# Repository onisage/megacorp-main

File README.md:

# MEGACORP-main
For all MEGACORP-related projects.

Created in collaboration with [baconspoon](github.com/baconspoon85) and [apfel](https://github.com/kilipan).

## Row Stagger

## Ortholinear

## Alpha Stagger

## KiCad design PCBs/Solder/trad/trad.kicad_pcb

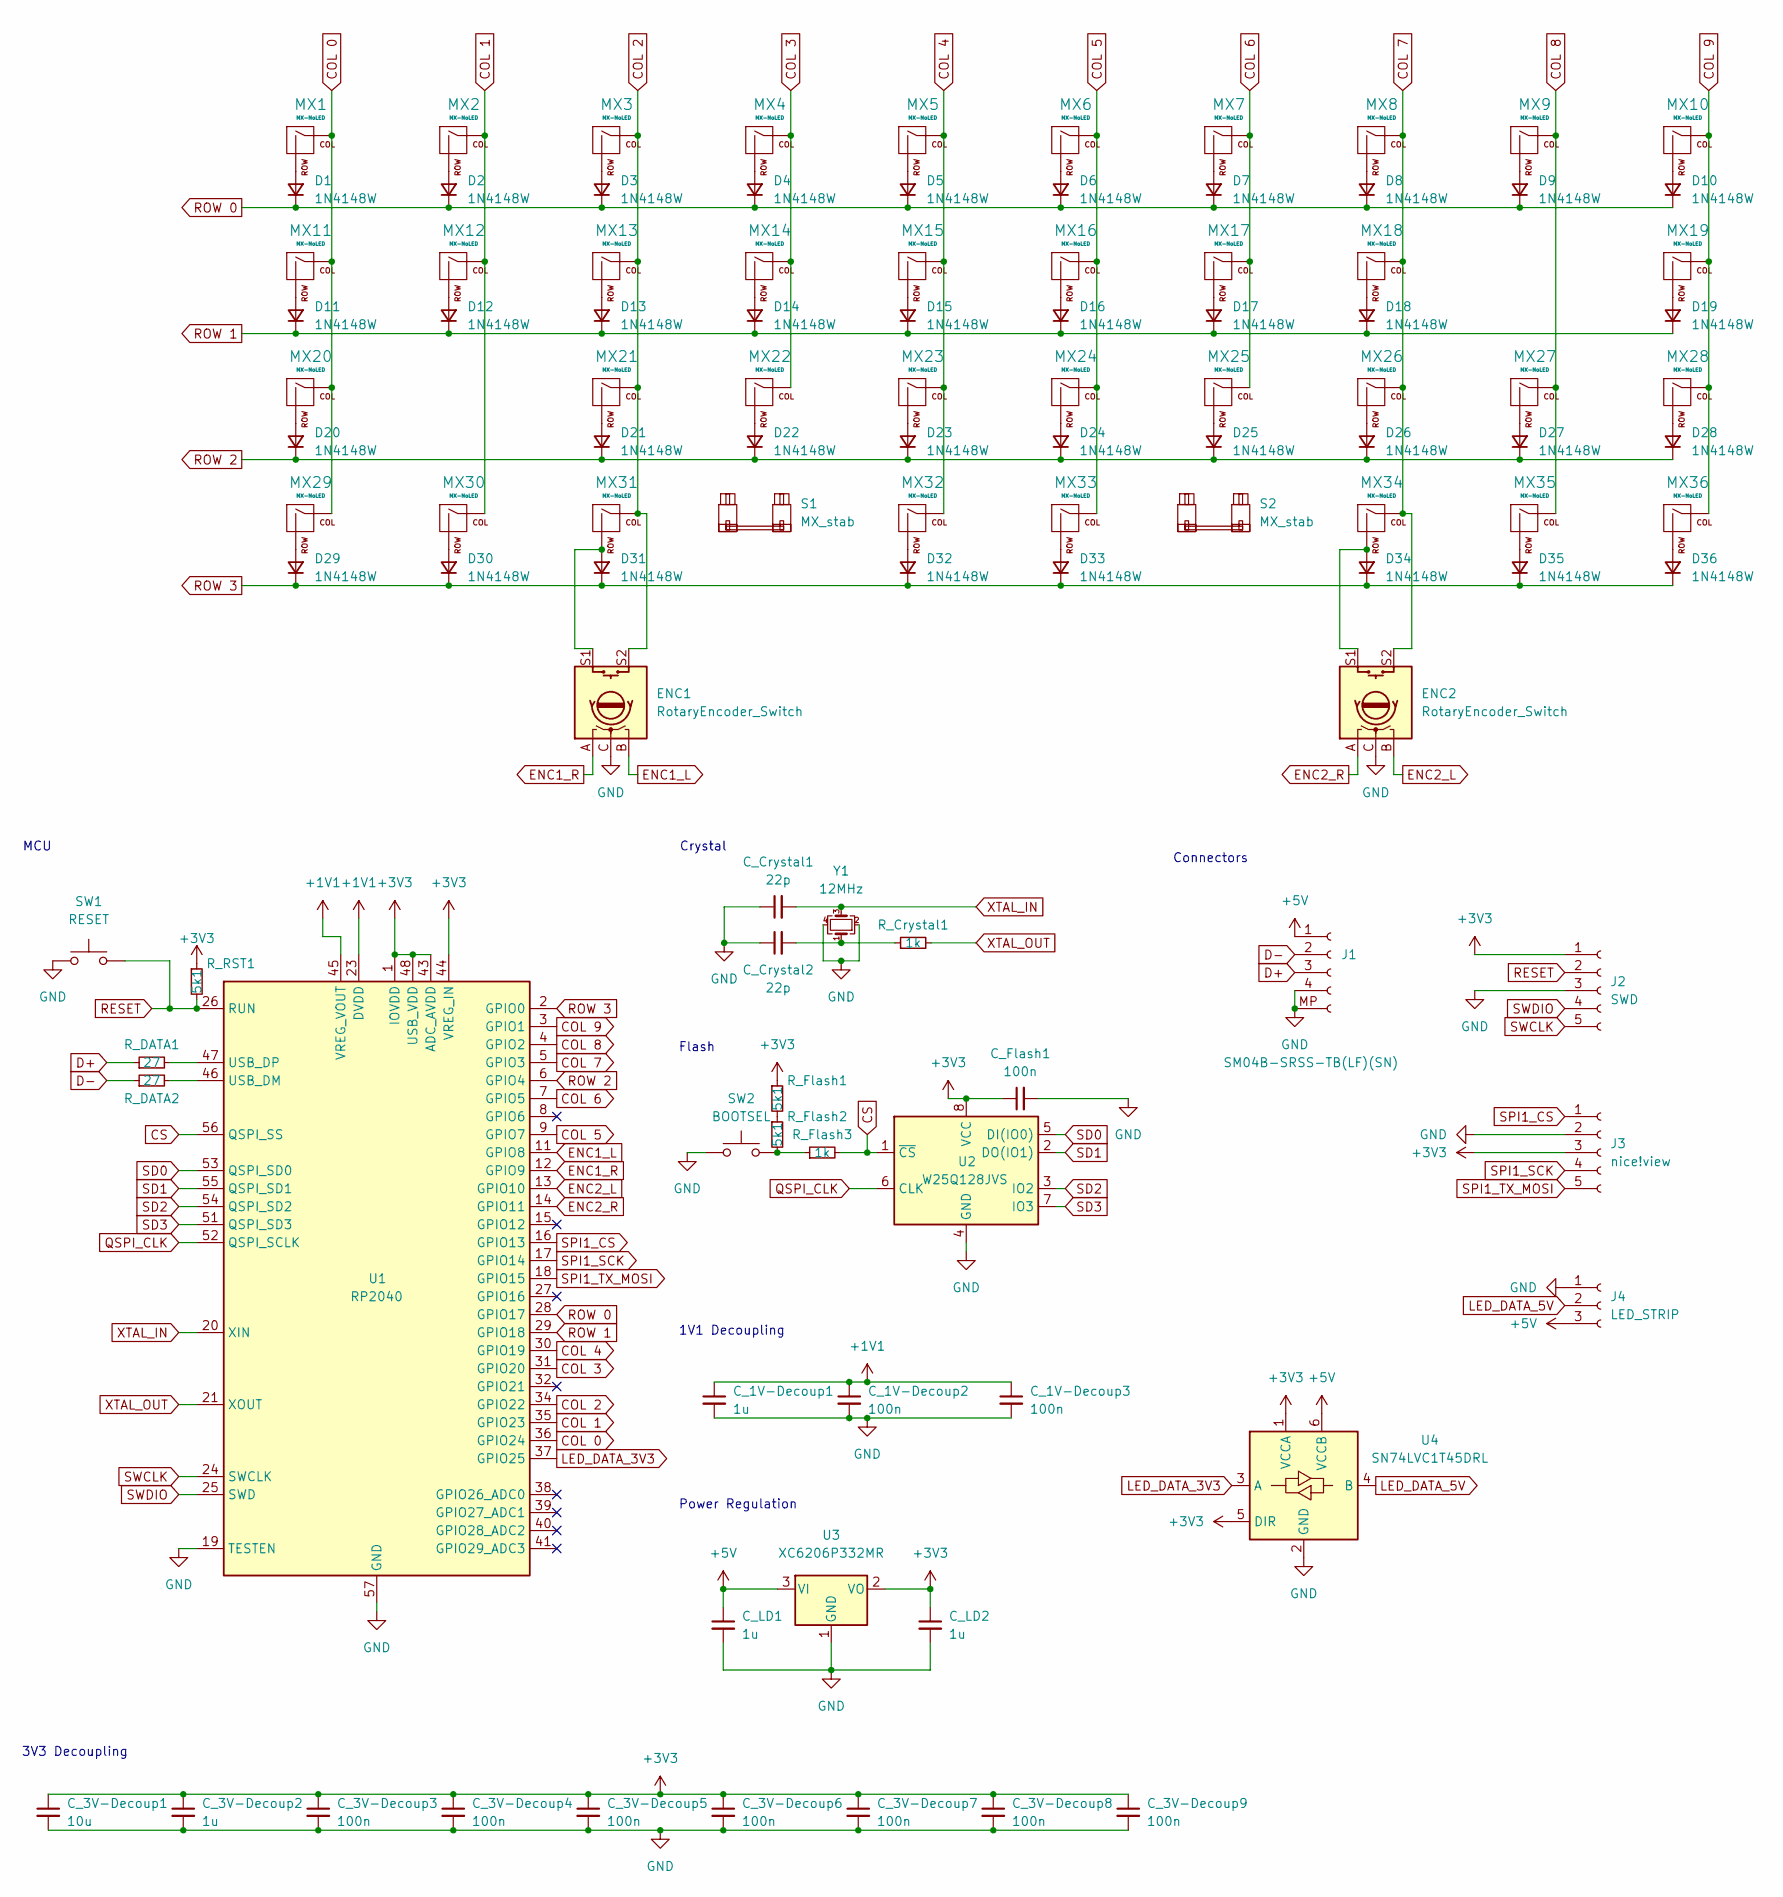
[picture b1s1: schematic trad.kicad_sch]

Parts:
C_1V-Decoup1, C_3V-Decoup2: 1u; C_0402_1005Metric
C_1V-Decoup2, C_1V-Decoup3, C_3V-Decoup3, C_3V-Decoup4, C_3V-Decoup5, C_3V-Decoup6, C_3V-Decoup7, C_3V-Decoup8, C_3V-Decoup9: 100n; C_0402_1005Metric
C_3V-Decoup1: 10u; C_0402_1005Metric
C_Crystal1, C_Crystal2: 22p; C_0402_1005Metric
C_Flash1: 100n; C_0402_1005Metric
C_LD1, C_LD2: 1u; C_0402_1005Metric
D1, D2, D3, D4, D5, D6, D7, D8, D9, D10, D11, D12, D13, D14, D15, D16, D17, D18, D19, D20, D21, D22, D23, D24, D25, D26, D27, D28, D29, D30, D31, D32, D33, D34, D35, D36: 1N4148W; D_SOD-123
ENC1, ENC2: RotaryEncoder_Switch; ROT_Alps_EC11E-Switch
J1: SM04B-SRSS-TB(LF)(SN); JST_SH_SM04B-SRSS-TB_1x04-1MP_P1.00mm_Horizontal; LCSC C160404
J2: SWD; PinHeader_1x05_P2.54mm_Vertical
J3: nice!view; PinHeader_1x05_P2.54mm_Vertical
J4: LED_STRIP; PinHeader_1x03_P2.54mm_Vertical
MX1, MX2, MX3, MX4, MX5, MX6, MX7, MX8, MX9, MX10, MX12, MX13, MX14, MX15, MX16, MX17, MX18, MX21, MX22, MX23, MX24, MX25, MX26, MX27, MX29, MX30, MX31, MX34, MX35, MX36: MX-NoLED; SW_Hybrid_Cherry_MX_Alps_1.00u
MX11, MX28: MX-NoLED; SW_Hybrid_Cherry_MX_Alps_1.25u
MX19, MX20: MX-NoLED; SW_Hybrid_Cherry_MX_Alps_1.75u
MX32, MX33: MX-NoLED; SW_Hybrid_Cherry_MX_Alps_2.00u
R_Crystal1: 1k; R_0402_1005Metric
R_DATA1, R_DATA2: 27; R_0402_1005Metric
R_Flash1, R_Flash2: 5k1; R_0402_1005Metric
R_Flash3: 1k; R_0402_1005Metric
R_RST1: 5k1; R_0402_1005Metric
S1, S2: MX_stab; STAB_MX_2u
SW1: RESET; SW_SPST_TL3342; LCSC C318884
SW2: BOOTSEL; SW_SPST_TL3342; LCSC C318884
U1: RP2040; QFN-56-1EP_7x7mm_P0.4mm_EP3.2x3.2mm_ThermalVias; LCSC C2040
U2: W25Q128JVS; SOIC-8_5.23x5.23mm_P1.27mm; LCSC C2613930
U3: XC6206P332MR; SOT-23; LCSC C5446
U4: SN74LVC1T45DRL; SOT-563
Y1: 12MHz; Crystal_SMD_3225-4Pin_3.2x2.5mm; LCSC C9002

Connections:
+1V1: C_1V-Decoup1.1, C_1V-Decoup2.1, C_1V-Decoup3.1, U1.23 (DVDD), U1.45 (VREG_VOUT), U1.50 (DVDD)
+3V3: C_3V-Decoup1.1, C_3V-Decoup2.1, C_3V-Decoup3.1, C_3V-Decoup4.1, C_3V-Decoup5.1, C_3V-Decoup6.1, C_3V-Decoup7.1, C_3V-Decoup8.1, C_3V-Decoup9.1, C_Flash1.1, C_LD2.1, J2.1, J3.3, R_Flash1.1, R_RST1.1, U1.1 (IOVDD), U1.10 (IOVDD), U1.22 (IOVDD), U1.33 (IOVDD), U1.42 (IOVDD), U1.43 (ADC_AVDD), U1.44 (VREG_IN), U1.48 (USB_VDD), U1.49 (IOVDD), U2.8 (VCC), U3.2 (VO), U4.1 (VCCA), U4.5 (DIR)
+5V: C_LD1.1, J1.1, J4.3, U3.3 (VI), U4.6 (VCCB)
COL 0: MX1.1 (COL), MX11.1 (COL), MX20.1 (COL), MX29.1 (COL), U1.36 (GPIO24)
COL 1: MX2.1 (COL), MX12.1 (COL), MX30.1 (COL), U1.35 (GPIO23)
COL 2: ENC1.S2, MX3.1 (COL), MX13.1 (COL), MX21.1 (COL), MX31.1 (COL), U1.34 (GPIO22)
COL 3: MX4.1 (COL), MX14.1 (COL), MX22.1 (COL), U1.31 (GPIO20)
COL 4: MX5.1 (COL), MX15.1 (COL), MX23.1 (COL), MX32.1 (COL), U1.30 (GPIO19)
COL 5: MX6.1 (COL), MX16.1 (COL), MX24.1 (COL), MX33.1 (COL), U1.9 (GPIO7)
COL 6: MX7.1 (COL), MX17.1 (COL), MX25.1 (COL), U1.7 (GPIO5)
COL 7: ENC2.S2, MX8.1 (COL), MX18.1 (COL), MX26.1 (COL), MX34.1 (COL), U1.5 (GPIO3)
COL 8: MX9.1 (COL), MX27.1 (COL), MX35.1 (COL), U1.4 (GPIO2)
COL 9: MX10.1 (COL), MX19.1 (COL), MX28.1 (COL), MX36.1 (COL), U1.3 (GPIO1)
CS: R_Flash3.2, U1.56 (QSPI_SS), U2.1 (~CS)
D+: J1.3, R_DATA1.1
D-: J1.2, R_DATA2.1
ENC1_L: ENC1.B, U1.11 (GPIO8)
ENC1_R: ENC1.A, U1.12 (GPIO9)
ENC2_L: ENC2.B, U1.13 (GPIO10)
ENC2_R: ENC2.A, U1.14 (GPIO11)
GND: C_1V-Decoup1.2, C_1V-Decoup2.2, C_1V-Decoup3.2, C_3V-Decoup1.2, C_3V-Decoup2.2, C_3V-Decoup3.2, C_3V-Decoup4.2, C_3V-Decoup5.2, C_3V-Decoup6.2, C_3V-Decoup7.2, C_3V-Decoup8.2, C_3V-Decoup9.2, C_Crystal1.1, C_Crystal2.1, C_Flash1.2, C_LD1.2, C_LD2.2, ENC1.C, ENC2.C, J1.4, J1.MP, J2.3, J3.2, J4.1, SW1.1, SW2.1, U1.19 (TESTEN), U1.57 (GND), U2.4 (GND), U3.1 (GND), U4.2 (GND), Y1.2, Y1.4
LED_DATA_3V3: U1.37 (GPIO25), U4.3 (A)
LED_DATA_5V: J4.2, U4.4 (B)
unnamed: C_Crystal2.2, R_Crystal1.1, Y1.1
unnamed: D1.2 (A), MX1.2 (ROW)
unnamed: D2.2 (A), MX2.2 (ROW)
unnamed: D3.2 (A), MX3.2 (ROW)
unnamed: D4.2 (A), MX4.2 (ROW)
unnamed: D5.2 (A), MX5.2 (ROW)
unnamed: D6.2 (A), MX6.2 (ROW)
unnamed: D7.2 (A), MX7.2 (ROW)
unnamed: D8.2 (A), MX8.2 (ROW)
unnamed: D9.2 (A), MX9.2 (ROW)
unnamed: D10.2 (A), MX10.2 (ROW)
unnamed: D11.2 (A), MX11.2 (ROW)
unnamed: D12.2 (A), MX12.2 (ROW)
unnamed: D13.2 (A), MX13.2 (ROW)
unnamed: D14.2 (A), MX14.2 (ROW)
unnamed: D15.2 (A), MX15.2 (ROW)
unnamed: D16.2 (A), MX16.2 (ROW)
unnamed: D17.2 (A), MX17.2 (ROW)
unnamed: D18.2 (A), MX18.2 (ROW)
unnamed: D19.2 (A), MX19.2 (ROW)
unnamed: D20.2 (A), MX20.2 (ROW)
unnamed: D21.2 (A), MX21.2 (ROW)
unnamed: D22.2 (A), MX22.2 (ROW)
unnamed: D23.2 (A), MX23.2 (ROW)
unnamed: D24.2 (A), MX24.2 (ROW)
unnamed: D25.2 (A), MX25.2 (ROW)
unnamed: D26.2 (A), MX26.2 (ROW)
unnamed: D27.2 (A), MX27.2 (ROW)
unnamed: D28.2 (A), MX28.2 (ROW)
unnamed: D29.2 (A), MX29.2 (ROW)
unnamed: D30.2 (A), MX30.2 (ROW)
unnamed: D31.2 (A), ENC1.S1, MX31.2 (ROW)
unnamed: D32.2 (A), MX32.2 (ROW)
unnamed: D33.2 (A), MX33.2 (ROW)
unnamed: D34.2 (A), ENC2.S1, MX34.2 (ROW)
unnamed: D35.2 (A), MX35.2 (ROW)
unnamed: D36.2 (A), MX36.2 (ROW)
unnamed: R_Flash1.2, R_Flash2.1
unnamed: R_Flash2.2, R_Flash3.1, SW2.2
unnamed: R_DATA2.2, U1.46 (USB_DM)
unnamed: R_DATA1.2, U1.47 (USB_DP)
QSPI_CLK: U1.52 (QSPI_SCLK), U2.6 (CLK)
RESET: J2.2, R_RST1.2, SW1.2, U1.26 (RUN)
ROW 0: D1.1 (K), D2.1 (K), D3.1 (K), D4.1 (K), D5.1 (K), D6.1 (K), D7.1 (K), D8.1 (K), D9.1 (K), D10.1 (K), U1.28 (GPIO17)
ROW 1: D11.1 (K), D12.1 (K), D13.1 (K), D14.1 (K), D15.1 (K), D16.1 (K), D17.1 (K), D18.1 (K), D19.1 (K), U1.29 (GPIO18)
ROW 2: D20.1 (K), D21.1 (K), D22.1 (K), D23.1 (K), D24.1 (K), D25.1 (K), D26.1 (K), D27.1 (K), D28.1 (K), U1.6 (GPIO4)
ROW 3: D29.1 (K), D30.1 (K), D31.1 (K), D32.1 (K), D33.1 (K), D34.1 (K), D35.1 (K), D36.1 (K), U1.2 (GPIO0)
SD0: U1.53 (QSPI_SD0), U2.5 (DI(IO0))
SD1: U1.55 (QSPI_SD1), U2.2 (DO(IO1))
SD2: U1.54 (QSPI_SD2), U2.3 (IO2)
SD3: U1.51 (QSPI_SD3), U2.7 (IO3)
SPI1_CS: J3.1, U1.16 (GPIO13)
SPI1_SCK: J3.4, U1.17 (GPIO14)
SPI1_TX_MOSI: J3.5, U1.18 (GPIO15)
SWCLK: J2.5, U1.24 (SWCLK)
SWDIO: J2.4, U1.25 (SWD)
XTAL_IN: C_Crystal1.2, U1.20 (XIN), Y1.3
XTAL_OUT: R_Crystal1.2, U1.21 (XOUT)

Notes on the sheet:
Power Regulation
Flash
MCU
3V3 Decoupling
Connectors
1V1 Decoupling
Crystal

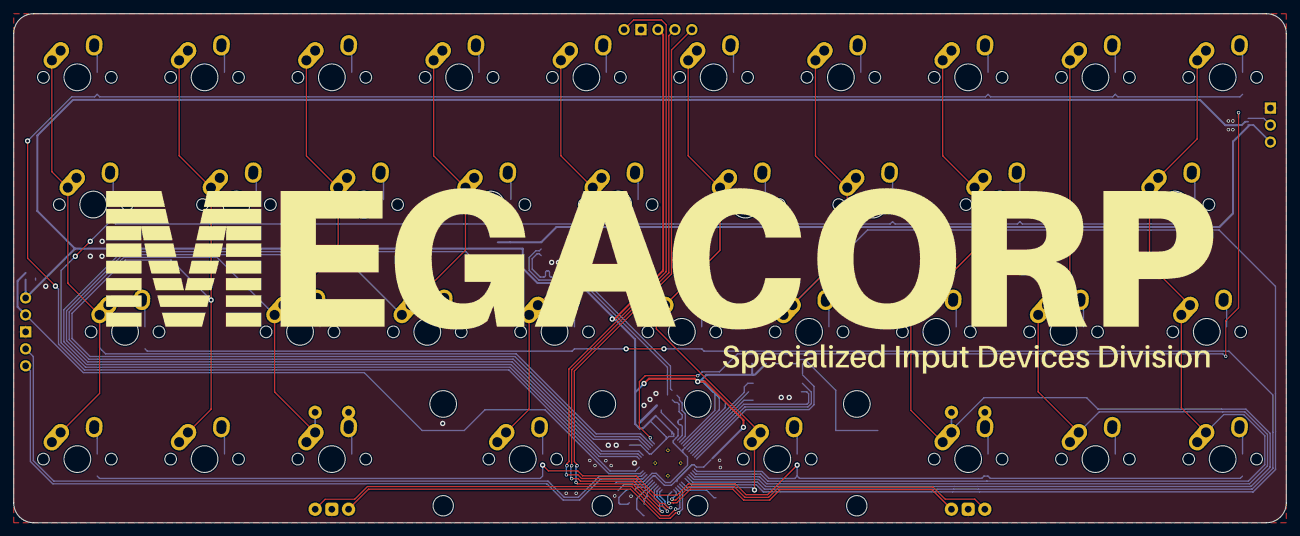
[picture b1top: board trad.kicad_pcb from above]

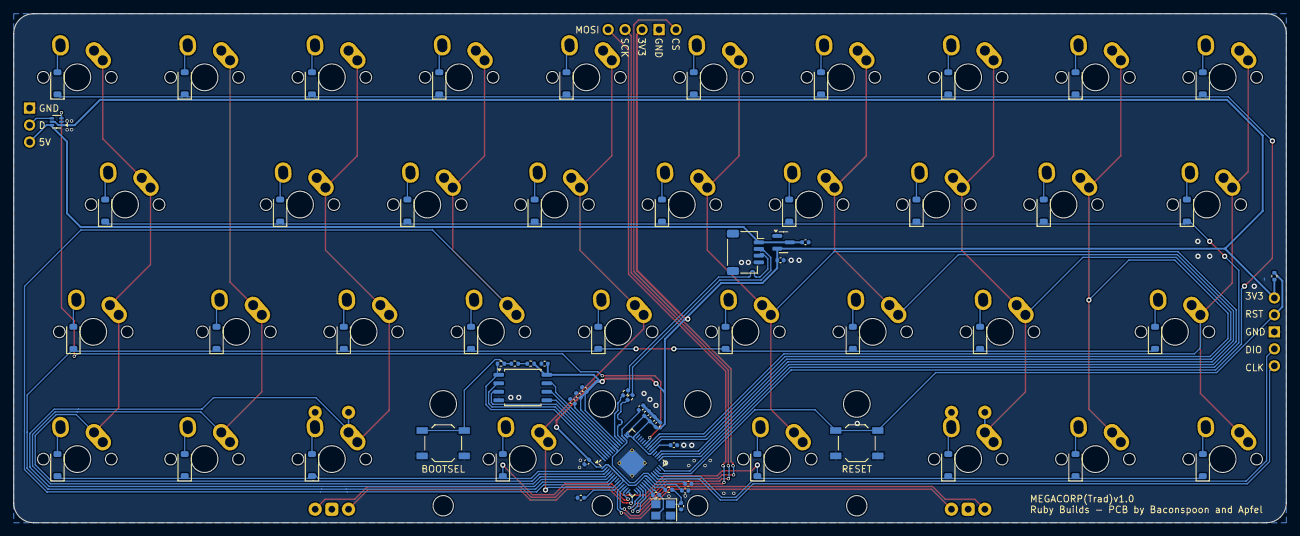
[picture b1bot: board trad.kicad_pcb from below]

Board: 2 copper layers, 190.5 x 76.2 mm, 111 parts (69 on the bottom side), 81 nets.

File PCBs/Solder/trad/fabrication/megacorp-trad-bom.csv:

Comment,Designator,Footprint,JLCPCB Part#(optional)
1uF,C_1V-Decoup1,C_0402_1005Metric,C52923
100nF,C_1V-Decoup2,C_0402_1005Metric,C2655418
100nF,C_1V-Decoup3,C_0402_1005Metric,C2655418
10uF,C_3V-Decoup1,C_0402_1005Metric,C19702
1uF,C_3V-Decoup2,C_0402_1005Metric,C52923
100nF,C_3V-Decoup3,C_0402_1005Metric,C2655418
100nF,C_3V-Decoup4,C_0402_1005Metric,C2655418
100nF,C_3V-Decoup5,C_0402_1005Metric,C2655418
100nF,C_3V-Decoup6,C_0402_1005Metric,C2655418
100nF,C_3V-Decoup7,C_0402_1005Metric,C2655418
100nF,C_3V-Decoup8,C_0402_1005Metric,C2655418
100nF,C_3V-Decoup9,C_0402_1005Metric,C2655418
22pF,C_Crystal1,C_0402_1005Metric,C1555
22pF,C_Crystal2,C_0402_1005Metric,C1555
100nF,C_Flash1,C_0402_1005Metric,C2655418
1uF,C_LD1,C_0402_1005Metric,C52923
1uF,C_LD2,C_0402_1005Metric,C52923
1N4148W,D1,D_SOD-123,C81598
1N4148W,D2,D_SOD-123,C81598
1N4148W,D3,D_SOD-123,C81598
1N4148W,D4,D_SOD-123,C81598
1N4148W,D5,D_SOD-123,C81598
1N4148W,D6,D_SOD-123,C81598
1N4148W,D7,D_SOD-123,C81598
1N4148W,D8,D_SOD-123,C81598
1N4148W,D9,D_SOD-123,C81598
1N4148W,D10,D_SOD-123,C81598
1N4148W,D11,D_SOD-123,C81598
1N4148W,D12,D_SOD-123,C81598
1N4148W,D13,D_SOD-123,C81598
1N4148W,D14,D_SOD-123,C81598
1N4148W,D15,D_SOD-123,C81598
1N4148W,D16,D_SOD-123,C81598
1N4148W,D17,D_SOD-123,C81598
1N4148W,D18,D_SOD-123,C81598
1N4148W,D19,D_SOD-123,C81598
1N4148W,D20,D_SOD-123,C81598
1N4148W,D21,D_SOD-123,C81598
1N4148W,D22,D_SOD-123,C81598
1N4148W,D23,D_SOD-123,C81598
1N4148W,D24,D_SOD-123,C81598
1N4148W,D25,D_SOD-123,C81598
1N4148W,D26,D_SOD-123,C81598
1N4148W,D27,D_SOD-123,C81598
1N4148W,D28,D_SOD-123,C81598
1N4148W,D29,D_SOD-123,C81598
1N4148W,D30,D_SOD-123,C81598
1N4148W,D31,D_SOD-123,C81598
1N4148W,D32,D_SOD-123,C81598
1N4148W,D33,D_SOD-123,C81598
1N4148W,D34,D_SOD-123,C81598
1N4148W,D35,D_SOD-123,C81598
1N4148W,D36,D_SOD-123,C81598
SM04B-SRSS-TB(LF)(SN),J1,JST_SH_SM04B-SRSS-TB_1x04-1MP_P1.00mm_Horizontal,C160404
1k,R_Crystal1,R_0402_1005Metric,C279987
27,R_DATA1,R_0402_1005Metric,C25100
27,R_DATA2,R_0402_1005Metric,C25100
5k1,R_Flash1,R_0402_1005Metric,C103086
5k1,R_Flash2,R_0402_1005Metric,C103086
1k,R_Flash3,R_0402_1005Metric,C279987
5k1,R_RST1,R_0402_1005Metric,C103086
RESET,SW1,SW_SPST_TL3342,C318884
BOOTSEL,SW2,SW_SPST_TL3342,C318884
RP2040,U1,QFN-56-1EP_7x7mm_P0.4mm_EP3.2x3.2mm_ThermalVias,C2040
W25Q128JVS,U2,SOIC-8_5.23x5.23mm_P1.27mm,C2613930
XC6206P332MR,U3,SOT-23,C6430947
12MHz,Y1,Crystal_SMD_3225-4Pin_3.2x2.5mm,C9002

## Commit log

2025-09-05 Delete MEGACORP-solder/MEGACORP-main directory
    Incomplete Upload
2025-09-05 Delete MEGACORP-hotswap/MEGACORP-main/alpha_hs directory
    Incomplete Upload
2025-09-05 Create temp
